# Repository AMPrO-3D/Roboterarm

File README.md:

# Roboterarm

Wir haben den Roboterarm von dem YouTuber "Skyentific" upgedatet, eine eigene Steuerelektronik dafür entwickelt und einen Softwarecontroller für den PC geschrieben, über die der Roboterarm grafisch programmiert werden kann.
<hr>
<br>

<br>

<hr>

<br>

<hr>

<br>
<hr>

Alle CAD-Dateien und die ursprüngliche Dokumnentation können über diesen Link auf dem [Repo von Skyentific](https://github.com/SkyentificGit/SmallRobotArm) abgerufen werden
<br>

Die Bestellliste um die Teile für den Roboter im europäischen Raum bestellen zu können, befindet sich [hier](/Warenkorb)
<br>

Die Eagle-Dateien für das Controllerboard finden sich [hier](/Elektronik/Eagle), die Gerberfiles [hier](/Elektronik/Gerber)
<br>
Nachdem das Board nach den EAGLE-Dateien aufgebaut wurde, können die Schrittmotor-Treiber, sowie der Teensy auf das Board aufgesteckt werden.
<br>
Anschließend muss die Firmware auf den Controller geladen werden, was in diesem [README](/Firmware) erklärt wird.

⋅⋅⋅

Wenn der Roboter selbst fertig aufgebaut ist, was nach der Dokumentation von Skyentific gemacht werden sollte, können Die Motoranschlussleitungen mit dem Controllerboard verbunden werden. Die Günstigste Variante wäre, die Anschlussleitungen direkt auf das Controllerboard zu löten. Soll es etwas Profesioneller aussehen, können stattdesen auch Stift und Buchsenleisten verwendet werden.

Als nächstes benötigt man ein altes PC-ATX-Netzteil. Wir haben so eines schon gehabt, aber dafür kann man jedes herkömmliche ATX-Netzteil, welches auf Amazon erhältlich ist verwenden. Die Anschlussleitung, die normalerweise auf das Mainboard aufgesteckt wird, das ist der Breiteste von den Steckern am Netzteil, sollte aufgtrennt werden, am besten kurz vor dem Stecker, und über die Anschlussblöcke anhand der Platinenbeschriftung angesteckt werden. Folgender Farbcode ist zwar eigentlich genormt, man sollte aber umbedingt mit einem Multimeter vor anschluss des Kabels überprüfen, ob an den entsprechenden Leitungen die richtigen Spannungen anliegen

⋅⋅⋅

Der Anschluss des Netzteils sollte unbedingt gewissenhaft durchgeführt werden, da bei fehlerhafter Versorgung unter Umstäden großer Schaden am Controllerboard entstehen kann.
<br>
um das System zu Starten, muss zu erst das Netzteil entsprechend der Herstellerbestimmungen mit Spannnung versorgt werden. Meist über ein Kaltgerätekabel in der Steckdose.

Damit der Controller ordungsgemäß funktioniert, muss bevor der Controller hochfährt der Roboter in  folgender Grundstellung stehen:

⋅⋅⋅

Als nächstes muss der Controller über ein USB-Micro Kabel an einem Computer angeschlossen werden, woraufhin der Controller hochfahren und die Schrittmotoren bestromt werden sollten. Dies erkennt man daran, das die Motoren ein Haltemoment aufbauen, wenn man die Motoren verucht manuell zu drehen. 

Wenn bis hierhin alles Funktioniert hat, kann man den Roboterarm über den [MotionController](/MotionController) gesteuert werden.

###### Anmerkung: Damit die Software funktionieren kann, müssen die Treiber über die Installation der Firmware installiert sein und auf dem PC die aktuelle JAVA-Version installiert sein

#### Wer Hilfestellung benötigt, Verbesserungsvorschläge hat etc, kann bitte einfach ein Issue aufmachen, dann helfen wir euch weiter

#### Die Software befindet sich in einem Early-Access Stadium, daher ist sie mit größter Vorsicht zu verwenden, da durch etwaige Softwarefehler der Roboter zum Beispiel ungewollte Bewegungen ausführt. Die Handhabung geschieht auf eigene Gefahr. Softwarefehler bitte über den Issue-Tab dieses Repos melden, damit wir schneller zu einem guten Ergebniss kommen können. Entwickler die Erfahrung mit Processing haben und sich an dem Projekt beteiligen möchten, können sich gerne über das Issue "Fehlende Entwickler" melden. Wir freuen uns über helfende Hände!

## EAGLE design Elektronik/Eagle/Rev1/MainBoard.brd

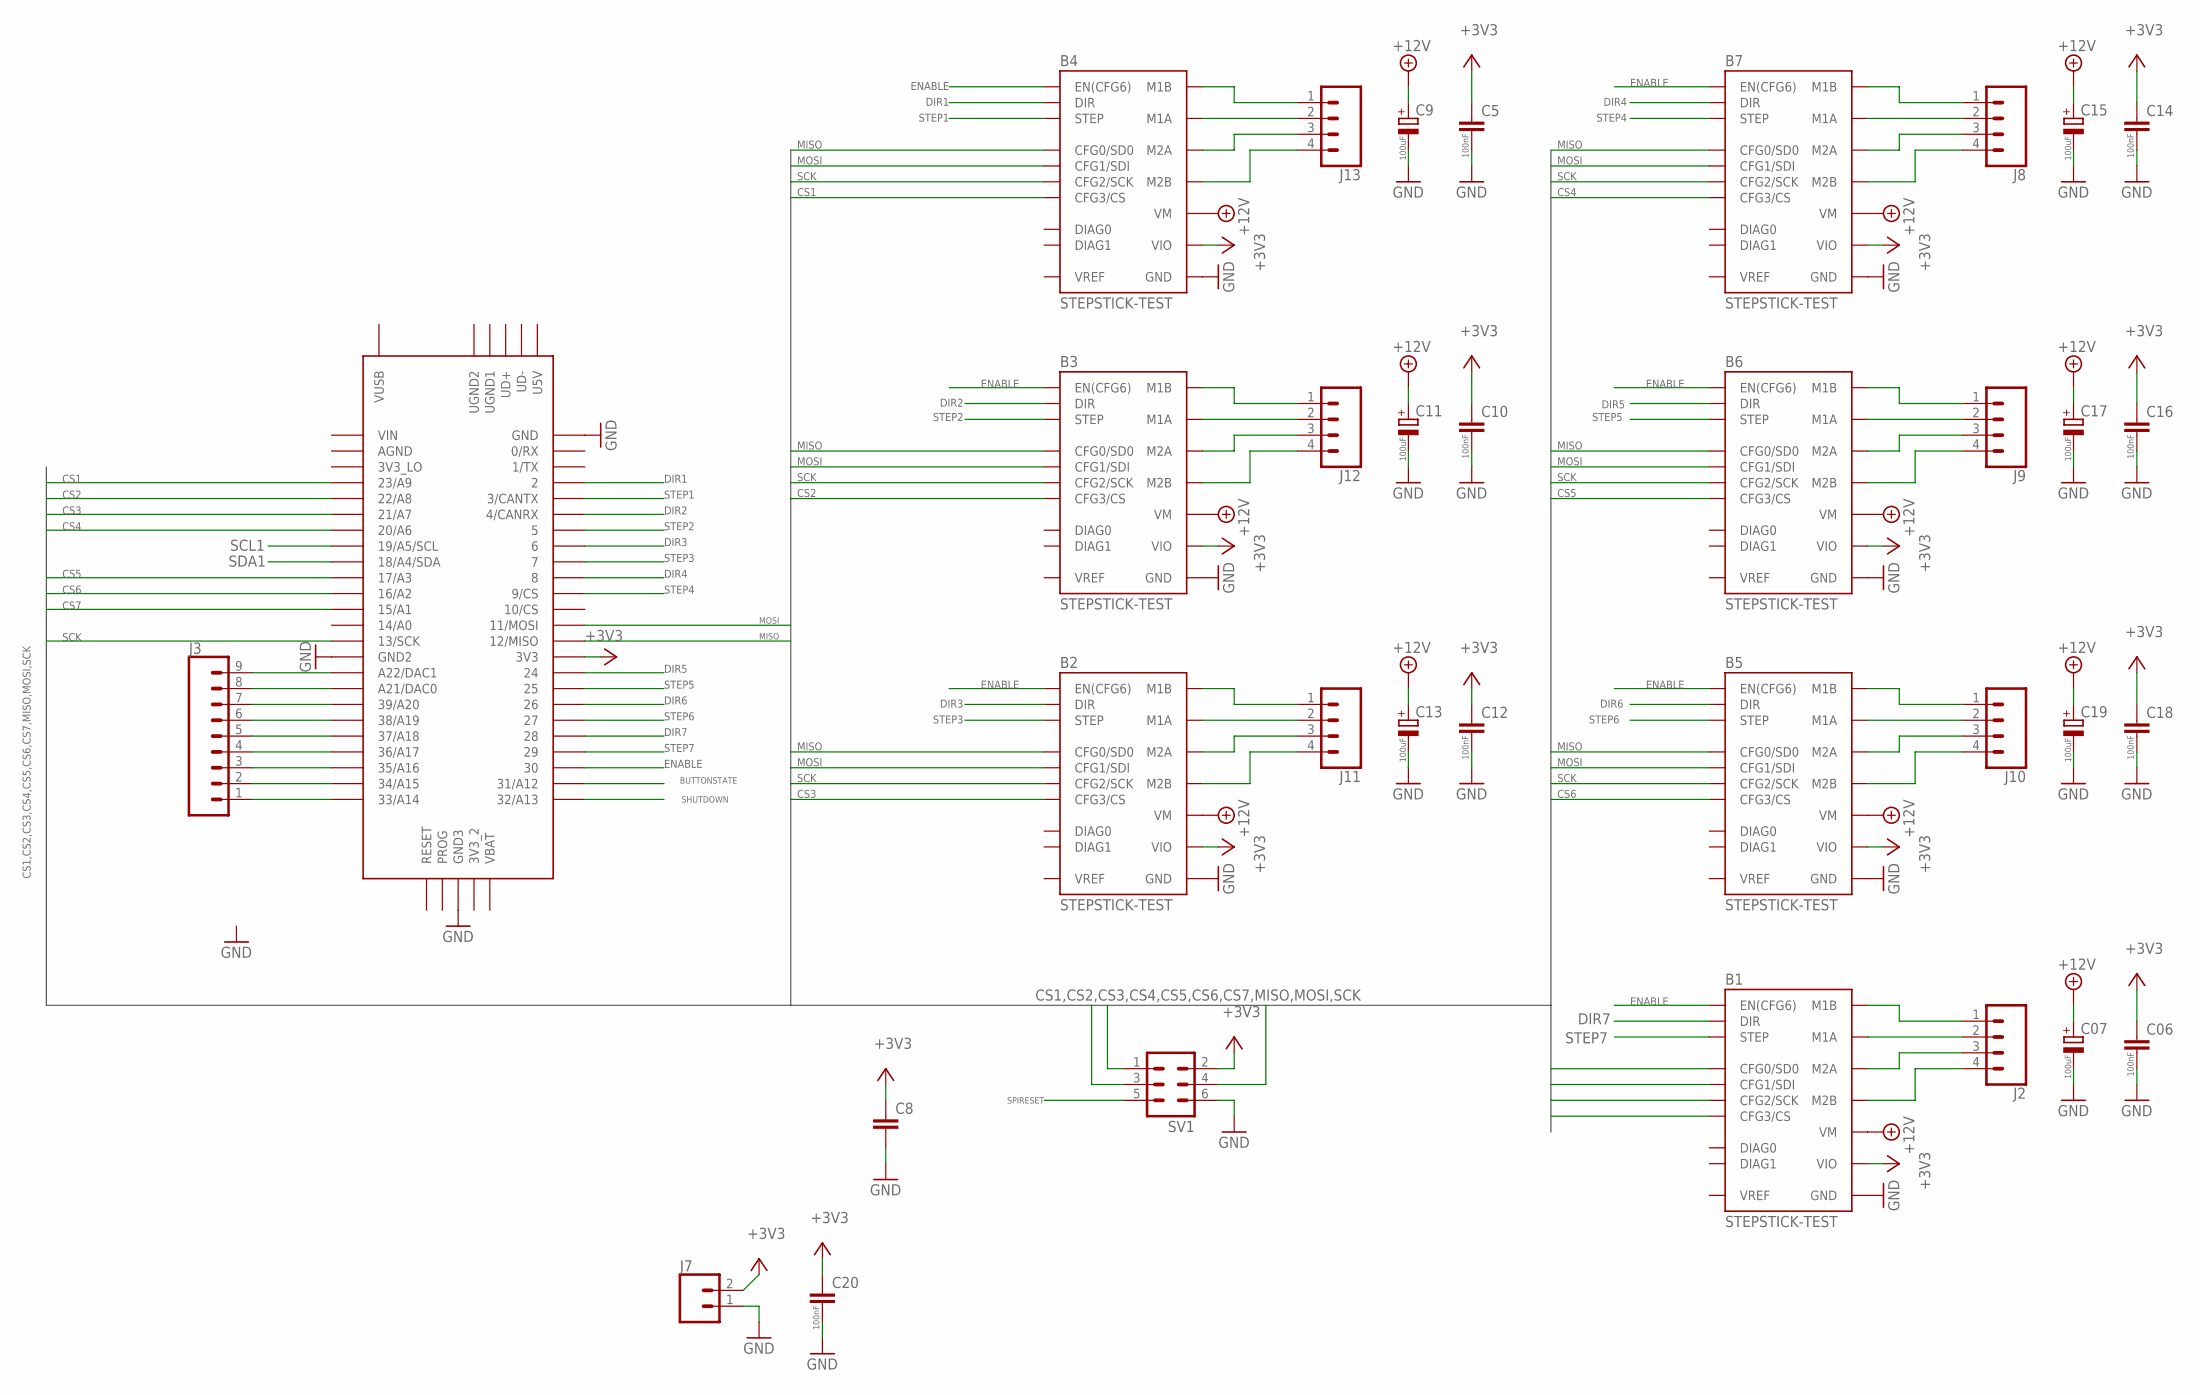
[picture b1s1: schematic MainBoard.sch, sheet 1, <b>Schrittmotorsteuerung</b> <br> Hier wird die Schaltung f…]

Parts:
B1, B2, B3, B4, B5, B6, B7: STEPSTICK-TEST
C5, C06, C10, C12, C14, C16, C18, C20: 100nF; C050-024X044
C07, C9, C11, C13, C15, C17, C19: 100uF; E2,5-6
C8: C-EU050-024X044; C050-024X044
J2, J8, J9, J10, J11, J12, J13: CONN_041X04_NO_SILK; 1X04_NO_SILK
J3: CONN_09LONGPADS; 1X09_LONGPADS
J7: CONN_02PTH3; 1X02_LONGPADS
SV1: MA03-2
U$1: TEENSY_4.1

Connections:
+3V3: B1.VIO, B2.VIO, B3.VIO, B4.VIO, B5.VIO, B6.VIO, B7.VIO, C5.1, C06.1, C8.1, C10.1, C12.1, C14.1, C16.1, C18.1, C20.1, J7.2, SV1.2, U$1.3V3; also elsewhere on the board
+12V: B1.VM, B2.VM, B3.VM, B4.VM, B5.VM, B6.VM, B7.VM, C07.+, C9.+, C11.+, C13.+, C15.+, C17.+, C19.+; also elsewhere on the board
BUTTONSTATE: U$1.31/A12; also elsewhere on the board
CS1: B4.CFG3 (CFG3/CS), U$1.23/A9
CS2: B3.CFG3 (CFG3/CS), U$1.22/A8
CS3: B2.CFG3 (CFG3/CS), U$1.21/A7
CS4: B7.CFG3 (CFG3/CS), U$1.20/A6
CS5: B6.CFG3 (CFG3/CS), U$1.17/A3
CS6: B5.CFG3 (CFG3/CS), U$1.16/A2
CS7: B1.CFG3 (CFG3/CS), U$1.15/A1
DIR1: B4.DIR, U$1.2
DIR2: B3.DIR, U$1.4/CANRX
DIR3: B2.DIR, U$1.6
DIR4: B7.DIR, U$1.8
DIR5: B6.DIR, U$1.24/A10 (24)
DIR6: B5.DIR, U$1.26/12 (26)
DIR7: B1.DIR, U$1.28
ENABLE: B1.EN (EN(CFG6)), B2.EN (EN(CFG6)), B3.EN (EN(CFG6)), B4.EN (EN(CFG6)), B5.EN (EN(CFG6)), B6.EN (EN(CFG6)), B7.EN (EN(CFG6)), U$1.30
GND: B1.GND@1 (GND), B1.GND@2 (GND), B2.GND@1 (GND), B2.GND@2 (GND), B3.GND@1 (GND), B3.GND@2 (GND), B4.GND@1 (GND), B4.GND@2 (GND), B5.GND@1 (GND), B5.GND@2 (GND), B6.GND@1 (GND), B6.GND@2 (GND), B7.GND@1 (GND), B7.GND@2 (GND), C5.2, C06.2, C07.-, C8.2, C9.-, C10.2, C11.-, C12.2, C13.-, C14.2, C15.-, C16.2, C17.-, C18.2, C19.-, C20.2, J7.1, SV1.6, U$1.GND, U$1.GND2, U$1.GND3; also elsewhere on the board
MISO: B1.NC/CFG0 (CFG0/SD0), B2.NC/CFG0 (CFG0/SD0), B3.NC/CFG0 (CFG0/SD0), B4.NC/CFG0 (CFG0/SD0), B5.NC/CFG0 (CFG0/SD0), B6.NC/CFG0 (CFG0/SD0), B7.NC/CFG0 (CFG0/SD0), SV1.1, U$1.12/MISO
MOSI: B1.CFG1 (CFG1/SDI), B2.CFG1 (CFG1/SDI), B3.CFG1 (CFG1/SDI), B4.CFG1 (CFG1/SDI), B5.CFG1 (CFG1/SDI), B6.CFG1 (CFG1/SDI), B7.CFG1 (CFG1/SDI), SV1.4, U$1.11/MOSI
unnamed: B1.M2B, J2.4
unnamed: B1.M2A, J2.3
unnamed: B1.M1A, J2.2
unnamed: B1.M1B, J2.1
unnamed: J3.1, U$1.33/A14
unnamed: J3.2, U$1.34/A15
unnamed: J3.3, U$1.35/A16
unnamed: J3.4, U$1.36/A17
unnamed: J3.5, U$1.37/A18
unnamed: J3.6, U$1.38/A19
unnamed: B2.M2B, J11.4
unnamed: B2.M2A, J11.3
unnamed: B2.M1A, J11.2
unnamed: B2.M1B, J11.1
unnamed: B3.M2B, J12.4
unnamed: B3.M2A, J12.3
unnamed: B3.M1A, J12.2
unnamed: B3.M1B, J12.1
unnamed: B4.M2B, J13.4
unnamed: B4.M2A, J13.3
unnamed: B4.M1A, J13.2
unnamed: B4.M1B, J13.1
unnamed: B5.M2B, J10.4
unnamed: B5.M2A, J10.3
unnamed: B5.M1A, J10.2
unnamed: B5.M1B, J10.1
unnamed: B6.M2B, J9.4
unnamed: B6.M2A, J9.3
unnamed: B6.M1A, J9.2
unnamed: B6.M1B, J9.1
unnamed: B7.M2B, J8.4
unnamed: B7.M2A, J8.3
unnamed: B7.M1A, J8.2
unnamed: B7.M1B, J8.1
unnamed: J3.7, U$1.39/A20
unnamed: J3.8, U$1.21/DAC0 (A21/DAC0)
unnamed: J3.9, U$1.A22/DAC1
SCK: B1.CFG2 (CFG2/SCK), B2.CFG2 (CFG2/SCK), B3.CFG2 (CFG2/SCK), B4.CFG2 (CFG2/SCK), B5.CFG2 (CFG2/SCK), B6.CFG2 (CFG2/SCK), B7.CFG2 (CFG2/SCK), SV1.3, U$1.13/SCK
SCL1: U$1.19/A5/SCL; also elsewhere on the board
SDA1: U$1.18/A4/SDA; also elsewhere on the board
SHUTDOWN: U$1.32/A13; also elsewhere on the board
SPIRESET: SV1.5
STEP1: B4.STEP, U$1.3/CANTX
STEP2: B3.STEP, U$1.5
STEP3: B2.STEP, U$1.7
STEP4: B7.STEP, U$1.9/CS
STEP5: B6.STEP, U$1.25/A11 (25)
STEP6: B5.STEP, U$1.27/A13 (27)
STEP7: B1.STEP, U$1.29

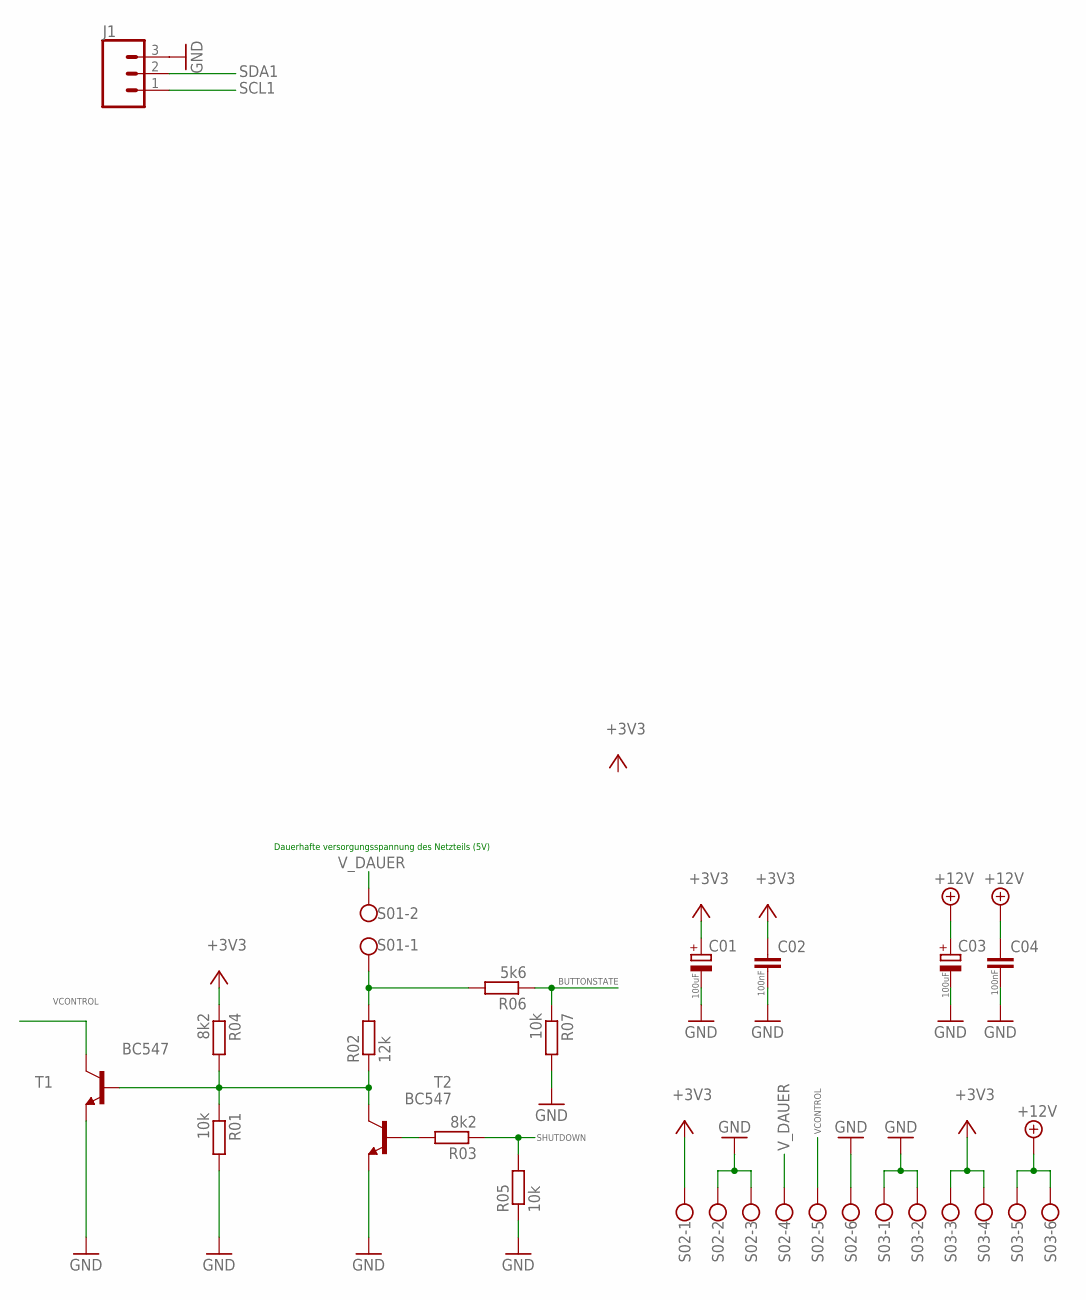
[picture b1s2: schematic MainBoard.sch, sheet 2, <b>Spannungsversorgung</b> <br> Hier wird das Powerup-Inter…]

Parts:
C01, C03: 100uF; E2,5-6
C02, C04: 100nF; C050-024X044
J1: CONN_03LONGPADS; 1X03_LONGPADS
R01, R05, R07: 10k; 0207/10
R02: 12k; 0207/10
R03, R04: 8k2; 0207/10
R06: 5k6; 0207/10
S01: W237-102
S02, S03: W237-6
T1, T2: BC547; TO92

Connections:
+3V3: C01.+, C02.1, R04.1, S02.1, S03.3, S03.4; also elsewhere on the board
+12V: C03.+, C04.1, S03.5, S03.6; also elsewhere on the board
BUTTONSTATE: R06.1, R07.1; also elsewhere on the board
GND: C01.-, C02.2, C03.-, C04.2, J1.3, R01.2, R05.1, R07.2, S02.2, S02.3, S02.6, S03.1, S03.2, T1.1 (E), T2.1 (E); also elsewhere on the board
unnamed: R01.1, R02.1, R04.2, T1.2 (B), T2.3 (C)
unnamed: R02.2, R06.2, S01.1
unnamed: R03.2, T2.2 (B)
SCL1: J1.1; also elsewhere on the board
SDA1: J1.2; also elsewhere on the board
SHUTDOWN: R03.1, R05.2; also elsewhere on the board
VCONTROL: S02.5, T1.3 (C)
V_DAUER: S01.2, S02.4

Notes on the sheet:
Dauerhafte versorgungsspannung des Netzteils (5V)

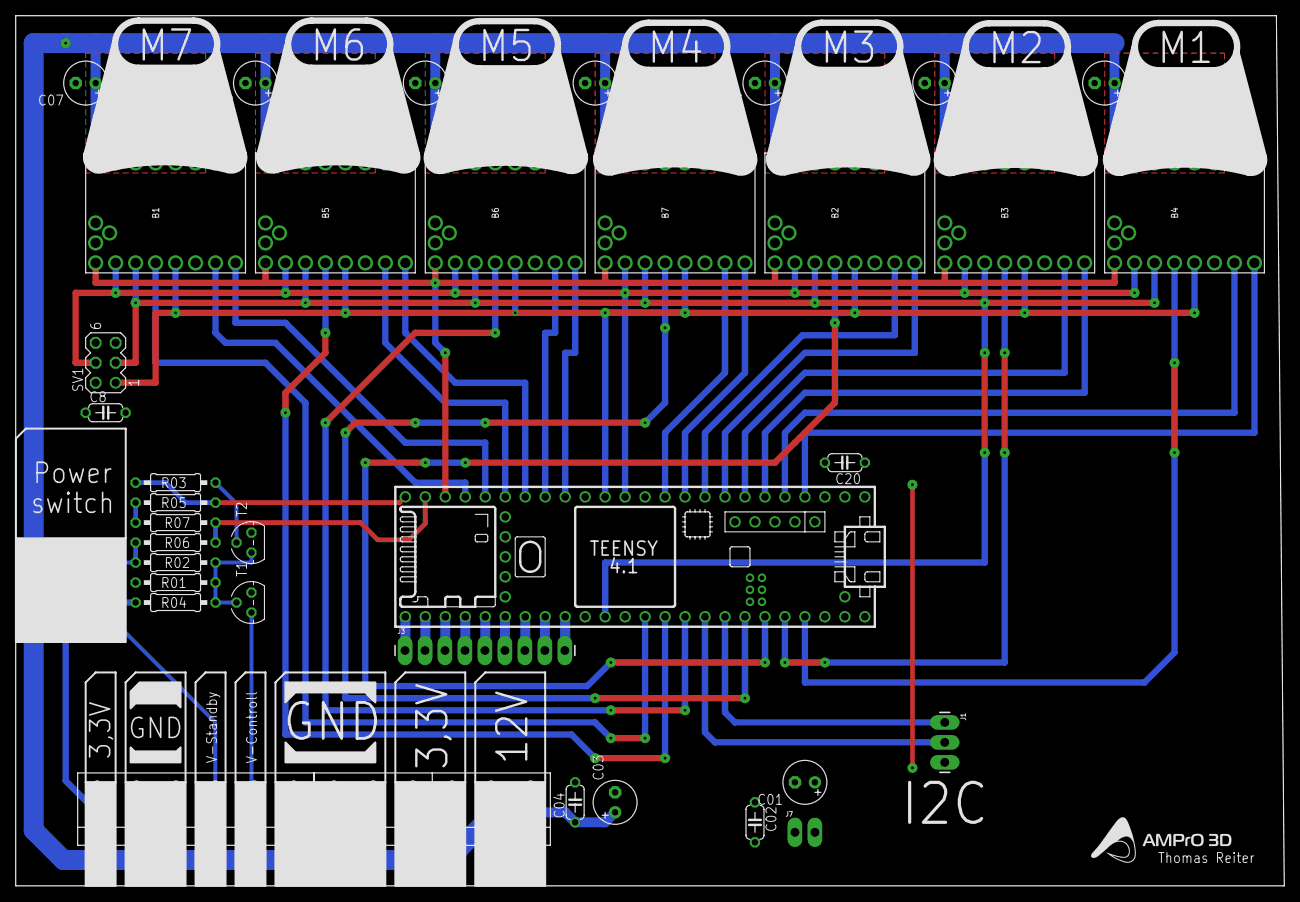
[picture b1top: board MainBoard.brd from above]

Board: 2 copper layers, 161.3 x 110.6 mm, 51 parts (0 on the bottom side), 74 nets.

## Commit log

2021-03-06 Create tt
2021-03-06 Create HowTo
2021-03-06 Rename HowTo.md to README.md
2021-03-06 Zusatzteile eingefügt
2021-03-06 Weitere Uploads
2021-03-07 Upload
2021-03-07 Hilfestellung
2021-04-03 Vergessenes nachträglich hochgeladen
2021-04-14 Fehlerausbesserung dank elektrofreak86
    Beim Layouten der Rev2 Elektronik ist mir ein Fehler unterlaufen, worauf ich durch den User elektrofreak86 aufmerksam gemacht wurde. -> Vielen Dank nochmal an Ihn! Dies wurde in der Version Rev3 ausg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

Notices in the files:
parts and their libraries:
SparkFun-Connectors: Licensing: Creative Commons ShareAlike 4.0 International - https://creativecommons.org/licenses/by-sa/4.0
